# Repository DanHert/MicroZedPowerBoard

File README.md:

# MicroZedPowerBoard

Breakout Board for MicroZed developement board.

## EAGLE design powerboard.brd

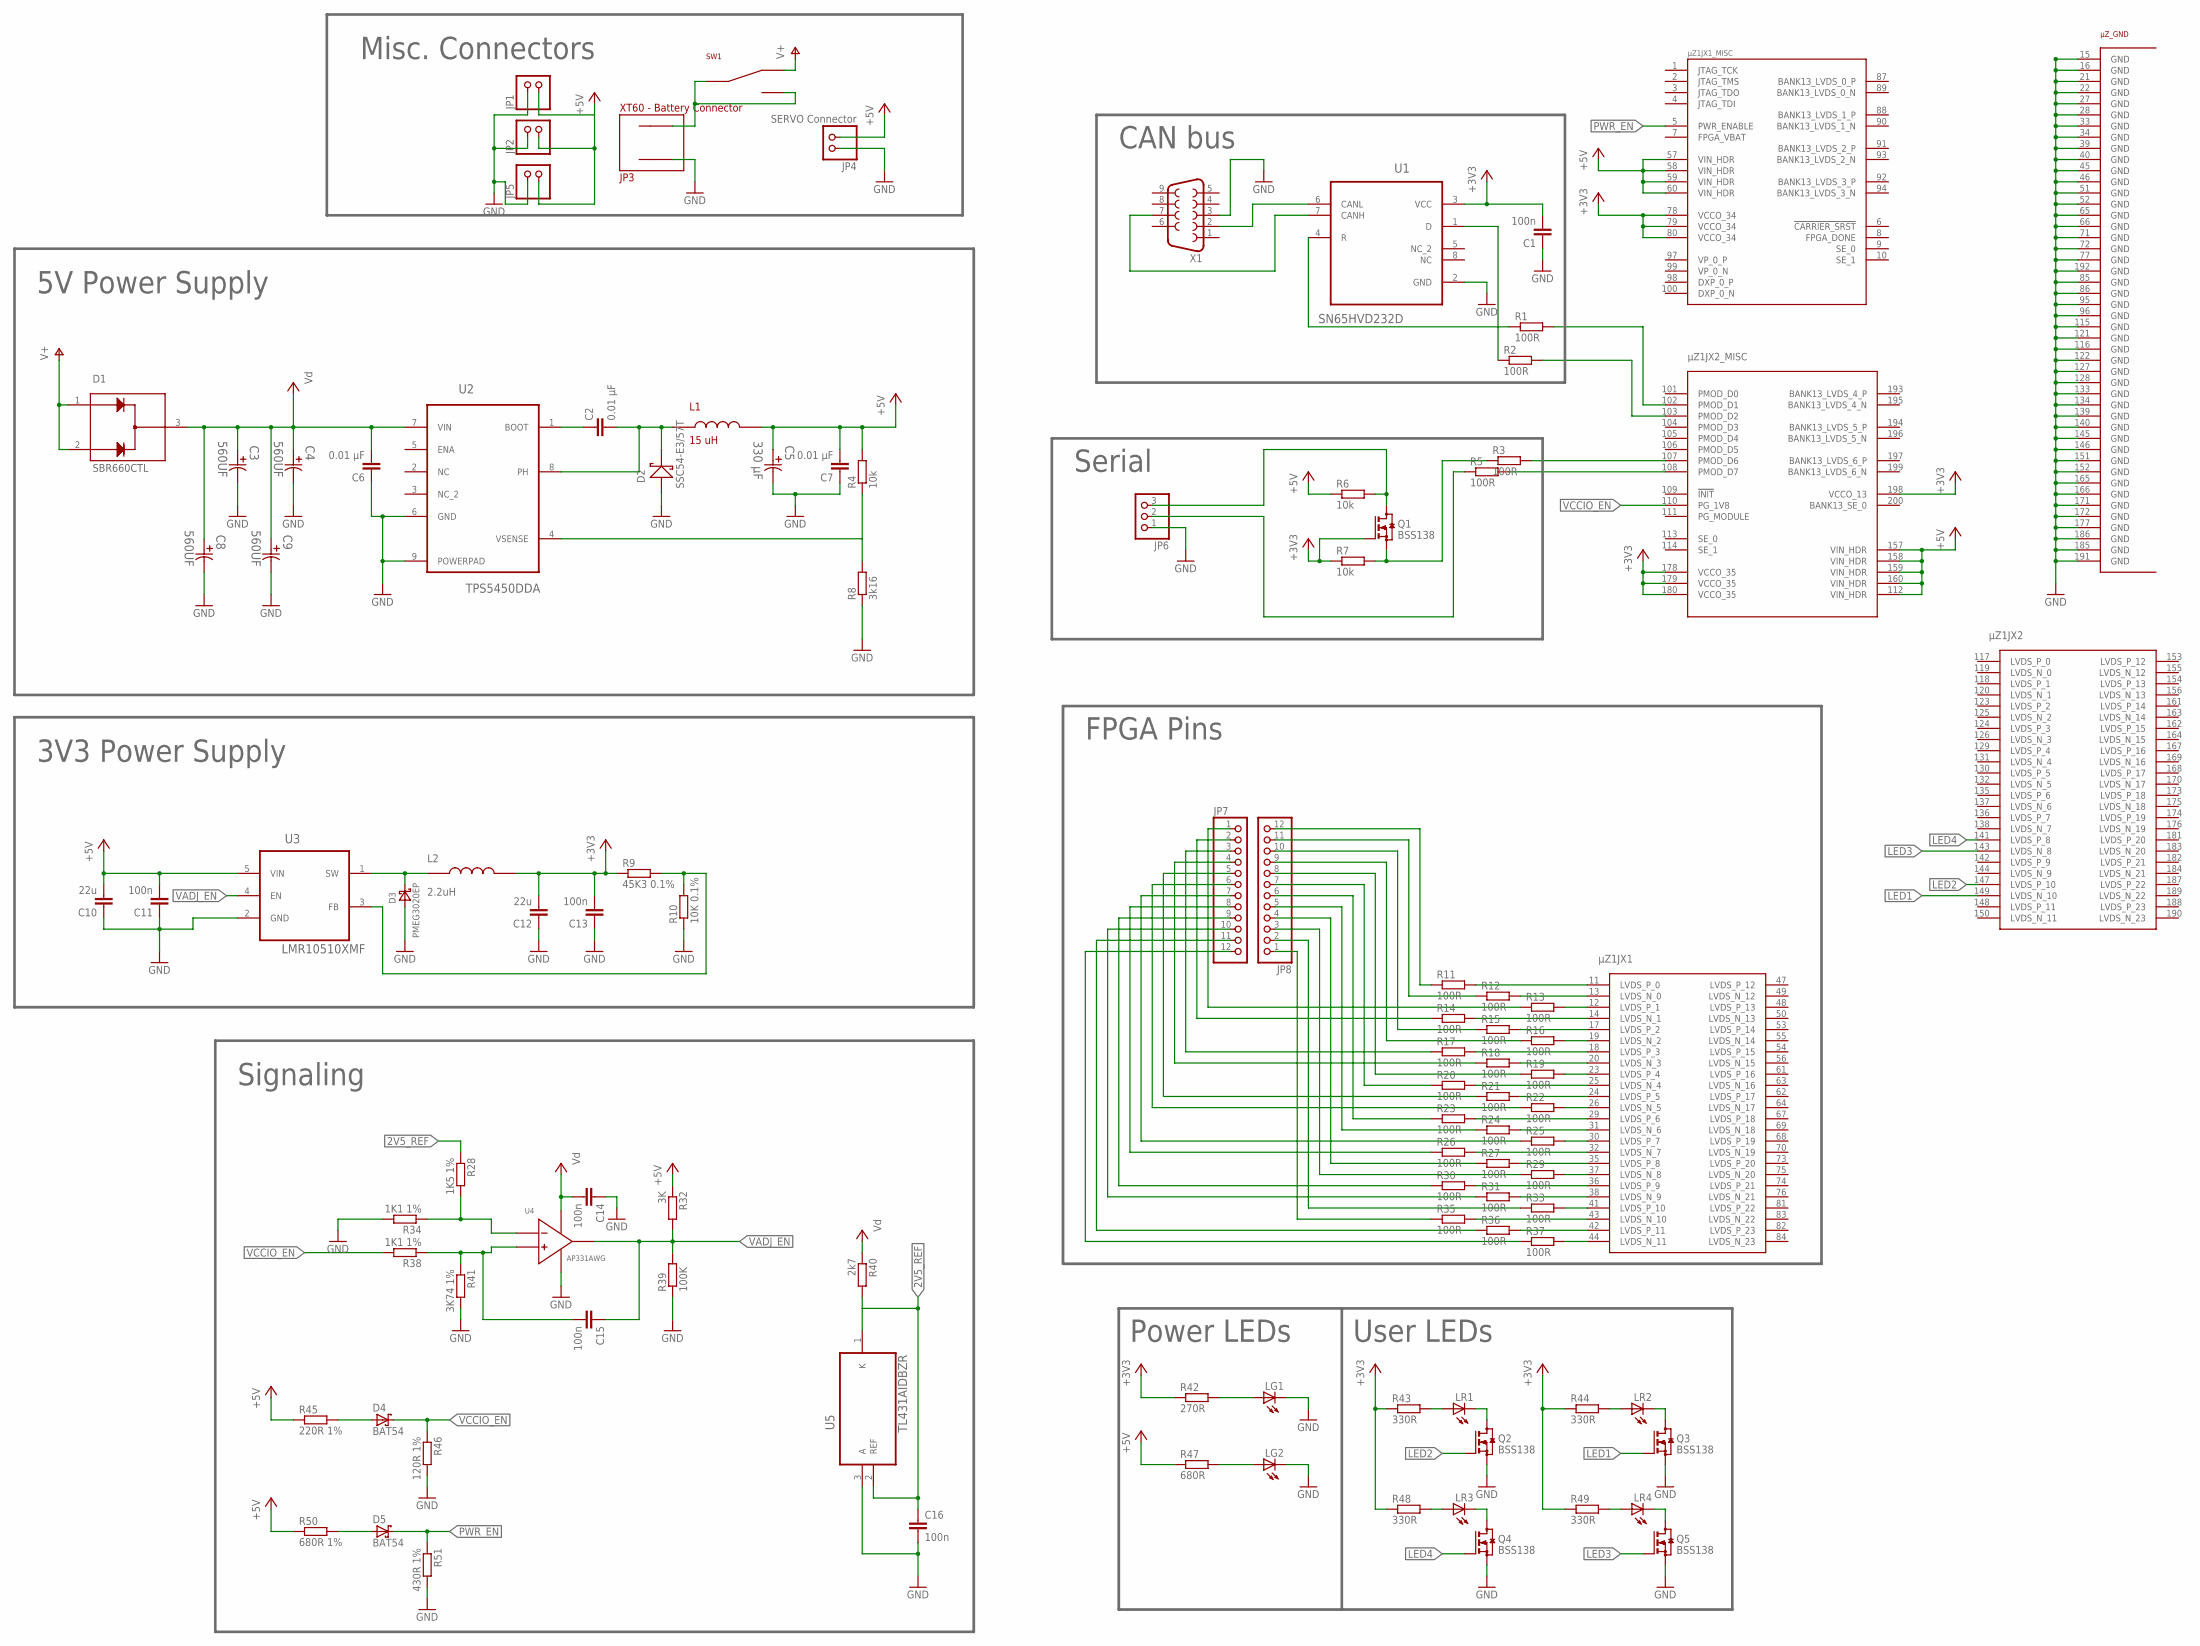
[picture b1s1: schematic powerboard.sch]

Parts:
C1, C11, C13, C14, C15, C16: 100n; C0805
C2, C6, C7: 0.01 µF; C0805
C3, C4, C8, C9: 560UF; CAPAE1030X1050N
C5: 330 µF; CAPAE660X800N
C10, C12: 22u; C0805
D1: SBR660CTL; TO252
D2: SSC54-E3/57T; DO-214AB
D3: PMEG3020EP; SOD128
D4, D5: BAT54; SOT23
JP1, JP2, JP5: PINHD-1X2; CUST
JP3: XT60 - Battery Connector; XT60
JP4: SERVO Connector; 1X02/90
JP6: PINHD-1X3; 1X03
JP7, JP8: PINHD-1X12; 1X12
L1: 15 uH; BOURNS
L2: 2.2uH; INDZYNQ2
LG1, LG2: LEDCHIP-LED0805; CHIP-LED0805
LR1, LR2, LR3, LR4: LEDCHIP-LED0805; CHIP-LED0805
Q1, Q2, Q3, Q4, Q5: BSS138; SOT23
R1, R2, R3, R5, R11, R12, R13, R14, R15, R16, R17, R18, R19, R20, R21, R22, R23, R24, R25, R26, R27, R29, R30, R31, R33, R35, R36, R37: 100R; R0805
R4, R6, R7: 10k; R0805
R8: 3k16; R0805
R9: 45K3 0.1%; R0805
R10: 10K 0.1%; R0805
R28: 1K5 1%; R0805
R32: 3K; R0805
R34, R38: 1K1 1%; R0805
R39: 100K; R0805
R40: 2k7; R0805
R41: 3K74 1%; R0805
R42: 270R; R0805
R43, R44, R48, R49: 330R; R0805
R45: 220R 1%; R0805
R46: 120R 1%; R0805
R47: 680R; R0805
R50: 680R 1%; R0805
R51: 430R 1%; R0805
SW1: SW
U1: SN65HVD232D; SOIC127P600X175-8N
U2: TPS5450DDA; SOIC127P600X170-9N
U3: LMR10510XMF; SOT95P290X145-5N
U4: AP331AWG; SOT95P290X145-5N
U5: TL431AIDBZR; SOT95P230X110-3N
X1: F09HP
µZ1: µZTS; µZ_E

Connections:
2V5_REF: C16.1, R28.1, R40.2, U5.1 (K), U5.2 (REF)
+3V3: C1.2, C12.2, C13.2, L2.P$2, Q1.1 (G), R7.1, R9.1, R42.1, R43.1, R44.1, R48.1, R49.1, U1.3 (VCC), µZ1.78 (VCCO_34), µZ1.79 (VCCO_34), µZ1.80 (VCCO_34), µZ1.178 (VCCO_35), µZ1.179 (VCCO_35), µZ1.180 (VCCO_35), µZ1.198 (VCCO_13)
+5V: C5.1, C7.2, C10.2, C11.2, JP1.P$2 (2), JP2.P$2 (2), JP4.2, JP5.P$2 (2), L1.P$2, R4.2, R6.1, R32.1, R45.1, R47.1, R50.1, U3.5 (VIN), µZ1.57 (VIN_HDR), µZ1.58 (VIN_HDR), µZ1.59 (VIN_HDR), µZ1.60 (VIN_HDR), µZ1.112 (VIN_HDR), µZ1.157 (VIN_HDR), µZ1.158 (VIN_HDR), µZ1.159 (VIN_HDR), µZ1.160 (VIN_HDR)
FPGA_VBAT: µZ1.7 (FPGA_VBAT)
GND: C1.1, C3.2, C4.2, C5.2, C6.1, C7.1, C8.2, C9.2, C10.1, C11.1, C12.1, C13.1, C14.1, C16.2, D2.A, D3.A, JP1.P$1 (1), JP2.P$1 (1), JP3.P$2 (PLUS), JP4.1, JP5.P$1 (1), JP6.1, LG1.C, LG2.C, Q2.2 (S), Q3.2 (S), Q4.2 (S), Q5.2 (S), R8.1, R10.1, R34.2, R39.1, R41.2, R46.2, R51.2, U1.2 (GND), U2.6 (GND), U2.9 (POWERPAD), U3.2 (GND), U4.2 (GND), U5.3 (A), X1.3, µZ1.15 (GND), µZ1.16 (GND), µZ1.21 (GND), µZ1.22 (GND), µZ1.27 (GND), µZ1.28 (GND), µZ1.33 (GND), µZ1.34 (GND), µZ1.39 (GND), µZ1.40 (GND), µZ1.45 (GND), µZ1.46 (GND), µZ1.51 (GND), µZ1.52 (GND), µZ1.65 (GND), µZ1.66 (GND), µZ1.71 (GND), µZ1.72 (GND), µZ1.77 (GND), µZ1.85 (GND), µZ1.86 (GND), µZ1.95 (GND), µZ1.96 (GND), µZ1.115 (GND), µZ1.116 (GND), µZ1.121 (GND), µZ1.122 (GND), µZ1.127 (GND), µZ1.128 (GND), µZ1.133 (GND), µZ1.134 (GND), µZ1.139 (GND), µZ1.140 (GND), µZ1.145 (GND), µZ1.146 (GND), µZ1.151 (GND), µZ1.152 (GND), µZ1.165 (GND), µZ1.166 (GND), µZ1.171 (GND), µZ1.172 (GND), µZ1.177 (GND), µZ1.185 (GND), µZ1.186 (GND), µZ1.191 (GND), µZ1.192 (GND)
LED1: Q3.1 (G), µZ1.149 (LVDS_N_10)
LED2: Q2.1 (G), µZ1.147 (LVDS_P_10)
LED3: Q5.1 (G), µZ1.143 (LVDS_N_8)
LED4: Q4.1 (G), µZ1.141 (LVDS_P_8)
unnamed: R1.1, U1.4 (R)
unnamed: JP8.12, R11.1
unnamed: U1.6 (CANL), X1.2
unnamed: R2.1, U1.1 (D)
unnamed: R22.2, µZ1.26 (LVDS_N_5)
unnamed: R21.2, µZ1.24 (LVDS_P_5)
unnamed: R20.2, µZ1.25 (LVDS_N_4)
unnamed: U1.7 (CANH), X1.7
unnamed: R1.2, µZ1.102 (PMOD_D1)
unnamed: R2.2, µZ1.103 (PMOD_D2)
unnamed: C2.1, U2.1 (BOOT)
unnamed: C2.2, D2.C, L1.P$1, U2.8 (PH)
unnamed: D5.1 (A), R50.2
unnamed: D3.C, L2.P$1, U3.1 (SW)
unnamed: R28.2, R34.1, U4.1 (IN-)
unnamed: R4.1, R8.2, U2.4 (VSENSE)
unnamed: R3.2, µZ1.107 (PMOD_D6)
unnamed: R5.2, µZ1.108 (PMOD_D7)
unnamed: R19.2, µZ1.23 (LVDS_P_4)
unnamed: JP6.2, R5.1
unnamed: R37.2, µZ1.44 (LVDS_N_11)
unnamed: R36.2, µZ1.42 (LVDS_P_11)
unnamed: R35.2, µZ1.43 (LVDS_N_10)
unnamed: R33.2, µZ1.41 (LVDS_P_10)
unnamed: R31.2, µZ1.38 (LVDS_N_9)
unnamed: R30.2, µZ1.36 (LVDS_P_9)
unnamed: R29.2, µZ1.37 (LVDS_N_8)
unnamed: R27.2, µZ1.35 (LVDS_P_8)
unnamed: R26.2, µZ1.32 (LVDS_N_7)
unnamed: R25.2, µZ1.30 (LVDS_P_7)
unnamed: R24.2, µZ1.31 (LVDS_N_6)
unnamed: R23.2, µZ1.29 (LVDS_P_6)
unnamed: JP7.1, R13.1
unnamed: JP8.11, R12.1
unnamed: JP7.2, R14.1
unnamed: JP8.10, R15.1
unnamed: JP7.3, R17.1
unnamed: JP8.9, R16.1
unnamed: JP7.4, R18.1
unnamed: JP8.8, R19.1
unnamed: JP7.5, R21.1
unnamed: JP8.7, R20.1
unnamed: JP7.6, R22.1
unnamed: JP8.6, R23.1
unnamed: Q1.2 (S), R3.1, R7.2
unnamed: JP6.3, Q1.3 (D), R6.2
unnamed: R18.2, µZ1.20 (LVDS_N_3)
unnamed: R17.2, µZ1.18 (LVDS_P_3)
unnamed: JP8.5, R24.1
unnamed: JP7.7, R25.1
unnamed: JP7.8, R26.1
unnamed: JP8.4, R27.1
unnamed: JP8.3, R29.1
unnamed: JP7.9, R30.1
unnamed: JP7.10, R31.1
unnamed: JP8.2, R33.1
unnamed: R16.2, µZ1.19 (LVDS_N_2)
unnamed: R15.2, µZ1.17 (LVDS_P_2)
unnamed: R14.2, µZ1.14 (LVDS_N_1)
unnamed: R13.2, µZ1.12 (LVDS_P_1)
unnamed: R12.2, µZ1.13 (LVDS_N_0)
unnamed: R11.2, µZ1.11 (LVDS_P_0)
unnamed: JP8.1, R35.1
unnamed: JP7.11, R36.1
unnamed: JP7.12, R37.1
unnamed: D4.1 (A), R45.2
unnamed: LG2.A, R47.2
unnamed: LR2.A, R44.2
unnamed: LG1.A, R42.2
unnamed: LR1.A, R43.2
unnamed: LR4.A, R49.2
unnamed: LR3.A, R48.2
unnamed: LR3.C, Q4.3 (D)
unnamed: LR1.C, Q2.3 (D)
unnamed: LR2.C, Q3.3 (D)
unnamed: LR4.C, Q5.3 (D)
unnamed: R9.2, R10.2, U3.3 (FB)
unnamed: C15.2, R38.1, R41.1, U4.3 (IN+)
unnamed: JP3.P$1 (MINUS), SW1.P$1, SW1.P$3
PWR_EN: D5.3 (C), R51.1, µZ1.5 (PWR_ENABLE)
V+: D1.1, D1.2, SW1.P$2
VADJ_EN: C15.1, R32.2, R39.2, U3.4 (EN), U4.4 (OUT)
VCCIO_EN: D4.3 (C), R38.2, R46.1, µZ1.110 (PG_1V8)
VD: C3.1, C4.1, C6.2, C8.1, C9.1, C14.2, D1.3, R40.1, U2.7 (VIN), U4.5 (VCC)

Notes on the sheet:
5V Power Supply
FPGA Pins
Serial
CAN bus
Power LEDs
User LEDs
3V3 Power Supply
Misc. Connectors
Signaling

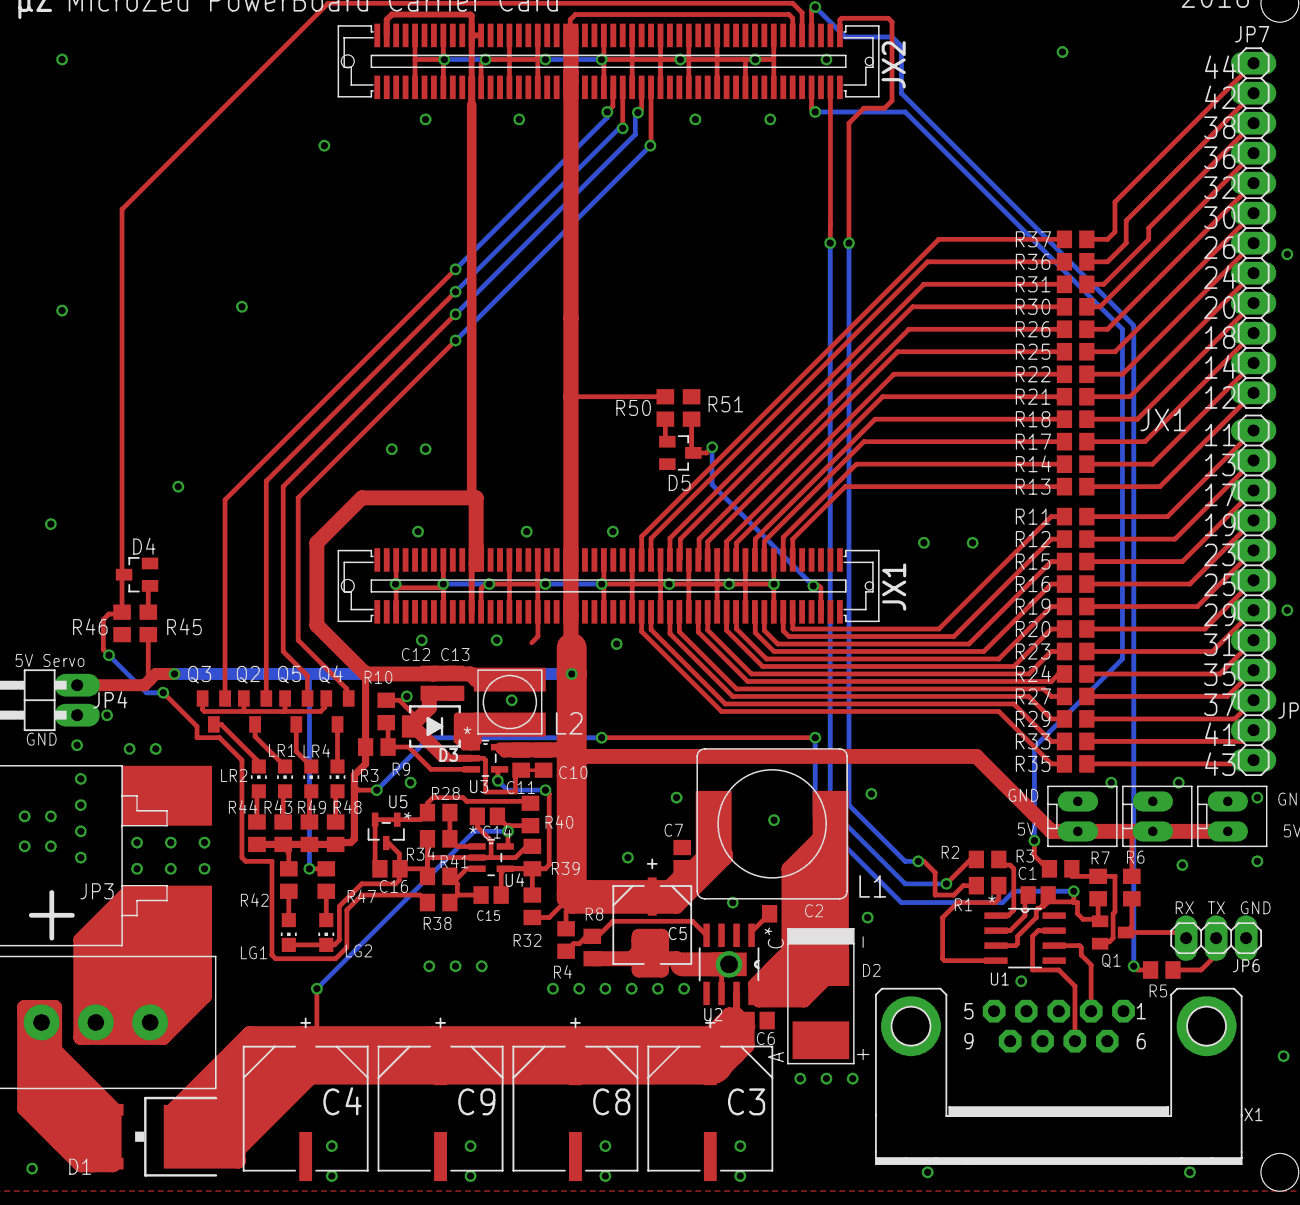
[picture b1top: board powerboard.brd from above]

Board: 2 copper layers, 101 parts (0 on the bottom side), 92 nets.

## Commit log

2017-01-06 Added schematics and board layout

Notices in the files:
parts and their libraries:
MyDiode: Creative Commons Attribution-ShareAlike 3.0 Unported (CC BY-SA 3.0), http://creativecommons.org/licenses/by-sa/3.0/.
